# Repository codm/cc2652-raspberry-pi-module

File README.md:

# cod.m ZigBee CC2652P Raspberry Pi module
[ZigBee CC2652 Raspberry Pi Coordinator](https://shop.codm.de/automation/zigbee/33/zigbee-cc2652p2-raspberry-pi-module) - a ZigBee Coordinator designed for the GPIO of the Raspberry Pi running Z-Stack Firmware 3.x - thanks to [Koenkk](https://github.com/Koenkk/).
The used CC2652P is the current generation of microcontrollers for ZigBee 3.x Coordinators and has an integrated power amplifier (+20dBm) for better coverage. 

According to [koenkk](https://github.com/Koenkk/Z-Stack-firmware/tree/master/coordinator) the CC2652 allows for up to 50 direct children and 100/200 routes directly on the coordinator. 
The size of a ZigBee mesh is not defined by the count of possible direct children at the coordinator, see https://www.zigbee2mqtt.io/information/FAQ.html#i-read-that-zigbee2mqtt-has-a-limit-of-20-devices-is-this-true

This module is the successor of our [CC2538 module](https://github.com/codm/cc2538-raspberry-pi-module). This time it is powered via the 5V rail of the Raspberry Pi with an LDO (Low Drop Out) voltage regulator. The CC2538 worked well on 3.3V directly but for the CC2652 we've decided to be not dependent on the internal voltage regulators of the Pi itself. 

You can buy a ready built coordinator, including external antenna at our webshop https://shop.codm.de/automation/zigbee/33/zigbee-cc2652p2-raspberry-pi-module or built on for non commercial use by yourself based on the files in this repository. Use the `bom.ulp` from Eagle to generate a parts list (BOM). 
If you can't get hold of the AP2112K you can also use an TLV75533P.

The 3D model of the RF-Star CC2652P could be found at GrabCad: https://grabcad.com/library/rf-star-cc2652p-module-1

# Running
To us the module directly on the serial interface on the GPIO of the Raspberry Pi, you have to free it up first. Either completely or by moving the Bluetooth UART to the mini-uart.
See https://www.raspberrypi.com/documentation/computers/configuration.html#configuring-uarts for a detailed explanation.

This is also explained in the manual (german): [Anleitung cod.m ZigBee CC2652 Raspberry Pi Modul](https://shop.codm.de/media/pdf/31/38/dd/20210427_ZigBee_CC2652_Raspberry_Pi_Modul_V02_Datenblatt_Anleitung-webnc4XN2YCGznNh.pdf)

If you want to use it with Home Assistant refer to this guide: https://github.com/MarijnPessers/cod.m-CC2538-CC2592-for-Home-Assistant

## zigbee2mqtt
Edit `data/configuration.yaml` accordingly: 

```
serial:
  port: /dev/ttyAMA0
  advanced: 
    baudrate: 115200 
    rtscts: false
```

## Homegear
Install `homegear-zigbee` and edit `/etc/homegear/families/zigbee.conf`: 

```
[Serial]
id = CC2652 
deviceType = serial

#use your own 16 bytes hexadecimal key! 
password = AABBCCDDEEFF11223344556677889900

device = /dev/ttyAMA0
```
Don't forget to comment in the `[]` block.

# Antenna
We recommend to use only external antennas as the module is close to the WiFi and Bluetooth module/antenna on the Raspberry Pi. But if you want to use the attached PCB antenna, rotate the resistor pointing to the u.FL socket by 90° so it connects the PCB trace.

# Firmware
We use Koenkk's Z-Stack 3.x Coordinator Firmware from https://github.com/Koenkk/Z-Stack-firmware/tree/master/coordinator/Z-Stack_3.x.0/bin, ZigStar Variant as it uses the same RF-BM-2652P2.

You can flash the firmware either by JTAG or directly from the Raspberry Pi using [cc2538-prog](https://github.com/1248/cc2538-prog/) - despite the name it also works with the CC2652.
The firmware has the needed serial bootloader enabled.

## JTAG
The 2x05 header is following the common [JTAG-Cortex-M0](https://www.segger.com/products/debug-probes/j-link/accessories/adapters/9-pin-cortex-m-adapter/) Layout.

Use `CC2652R1F` and `JTAG`@4000kHz.

## Serial via GPIO

### cc2538-bsl (preferred)
Install python3 if not alreay present with `sudo apt update && sudo apt-get install python3-pip` and install the needed python libraries `sudo pip3 install pyserial intelhex`.

Download or checkout [cc2538-bsl](https://github.com/JelmerT/cc2538-bsl) into a directory. After that download and extract the wanted coordinator firmware from [https://github.com/Koenkk/Z-Stack-firmware/tree/develop/coordinator/Z-Stack_3.x.0/bin](https://github.com/Koenkk/Z-Stack-firmware/tree/master/coordinator/Z-Stack_3.x.0/bin) - for the cod.m CC2652 Raspberry Pi module you'll need `CC1352P2_CC2652P_launchpad_*.zip` as listed on Koenkk's GitHub.

Please check that you zigbee software is not running anymore an nothing is accessing the serial device where the zigbee module is plugged in (`/dev/ttyAMA0`).

While connected and powered through the Pi, hold down the flash button on the module and press reset shortly while still holding flash. The CC2652 should now be in the bootloder.

To flash type `python3 cc2538-bsl.py -p /dev/ttyAMA0 -evw CC1352P2_CC2652P_launchpad_coordinator_20211217.hex` in the appropriate directory. Change the filename of the .hex-file accordingly.

The output looks something like this: 
```
pi@zigbee:~/cc2538-bsl $ python3 cc2538-bsl.py -evw -p /dev/ttyAMA0 ../CC1352P2_CC2652P_launchpad_coordinator_20211217.hex 
Opening port /dev/ttyAMA0, baud 500000
Reading data from ../CC1352P2_CC2652P_launchpad_coordinator_20211217.hex
Your firmware looks like an Intel Hex file
Connecting to target...
CC1350 PG2.0 (7x7mm): 352KB Flash, 20KB SRAM, CCFG.BL_CONFIG at 0x00057FD8
Primary IEEE Address: 00:12:4B:00:25:8F:18:32
    Performing mass erase
Erasing all main bank flash sectors
    Erase done
Writing 360448 bytes starting at address 0x00000000
Write 104 bytes at 0x00057F980
    Write done                                
Verifying by comparing CRC32 calculations.
    Verified (match: 0xba5c19c5)
```

After that hit the reset button on the module and start your zigbee software again. Maybe you have to replug the module or powercycle the pi.

Thanks to Alex for the documentation of that way.
Alternatively you can use https://github.com/electrolama/llama-bsl but I did not test this yet.

### cc2538-prog
Install and compile [cc2538-prog](https://github.com/1248/cc2538-prog/).

While connected and powered through the Pi, hold down the `flash` button on the module and press `reset` shortly while still holding `flash`. The CC2652 should now be in the bootloder.

Then execute `./cc2538-prog -d /dev/ttyAMA0 -f CC1352P2_CC2652P_launchpad_coordinator_20210120.hex `

The output should look like this: 
```
ping ok
Bootloader detected
Erasing page 0
Erasing page 1
[...]
Erasing page 254
Erasing page 255
Writing 16 bytes to 0x00200000
Writing 16 bytes to 0x00200010
[...]
Writing 16 bytes to 0x0023C7F0
Writing 12 bytes to 0x0027FFD4
```

After that reset the module using the corresponding button. 
It happened sometimes that I had to replug the module to get it to work again. 

# Thanks
* @koenkk Z-Stack Firmware - https://github.com/Koenkk/Z-Stack-firmware
* @1248 cc2538-prog - https://github.com/1248/cc2538-prog/

# License
[CC-BY-NC-SA 3.0](https://creativecommons.org/licenses/by-nc-sa/3.0/)

cod.m GmbH, Patrik Mayer, 2021

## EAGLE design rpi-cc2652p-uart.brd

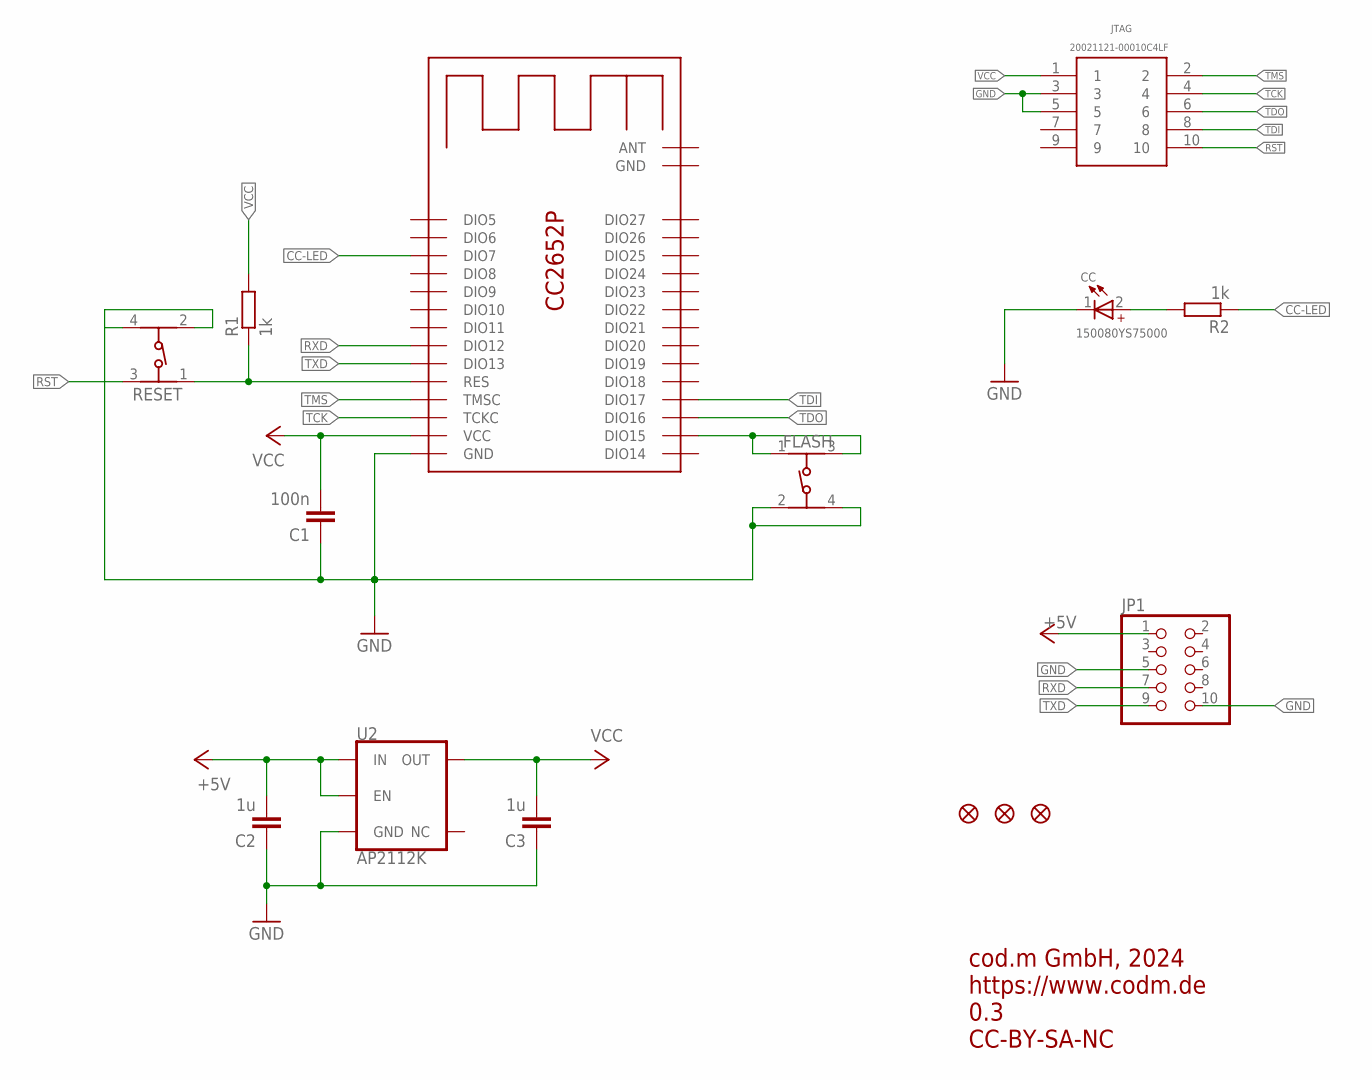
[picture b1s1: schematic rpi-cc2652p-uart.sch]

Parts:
C1: 100n; C0603K
C2, C3: 1u; C0805
CC: 150080YS75000; WL-SMCW_0805
FD1, FD2, FD3: FIDUCIAL1X2; FIDUCIAL-1X2
FLASH: 434153017835
JP1: PINHD-2X5; 2X05
JTAG: 20021121-00010C4LF; 2002112100010C4LF
R1, R2: 1k; R0603RF
RESET: 434153017835
U1: CC2652P2-DUOWEISI
U2: AP2112K; SOT23-5

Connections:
+5V: C2.2, JP1.1, U2.1 (IN), U2.3 (EN)
CC-LED: R2.1, U1.DIO7
FLASH: FLASH.1, FLASH.3 (2), U1.DIO15
GND: C1.1, C2.1, C3.1, CC.1 (-), FLASH.2 (3), FLASH.4, JP1.5, JP1.10, JTAG.3, JTAG.5, RESET.2 (3), RESET.4, U1.GND, U2.2 (GND)
unnamed: CC.2 (+), R2.2
RST: JTAG.10, R1.1, RESET.1, RESET.3 (2), U1.RES
RXD: JP1.7, U1.DIO12
TCK: JTAG.4, U1.TCKC
TDI: JTAG.8, U1.DIO17
TDO: JTAG.6, U1.DIO16
TMS: JTAG.2, U1.TMSC
TXD: JP1.9, U1.DIO13
VCC: C1.2, C3.2, JTAG.1, R1.2, U1.VCC, U2.5 (OUT)

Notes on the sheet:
cod.m GmbH, 2024 https://www.codm.de 0.3 CC-BY-SA-NC

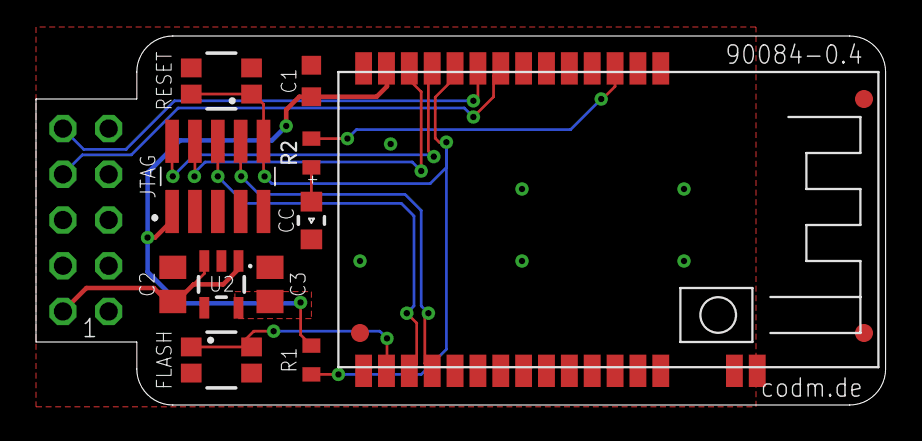
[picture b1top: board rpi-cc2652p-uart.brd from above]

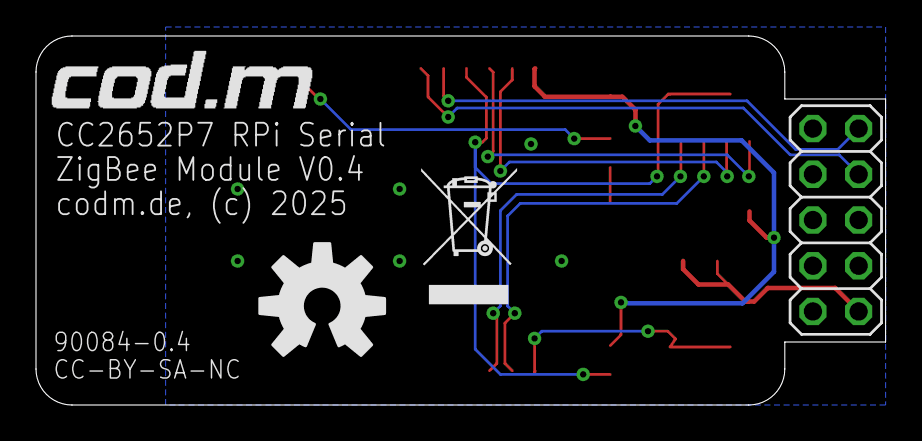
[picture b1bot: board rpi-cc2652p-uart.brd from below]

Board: 2 copper layers, 47.2 x 20.5 mm, 18 parts (4 on the bottom side), 13 nets.

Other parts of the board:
U$2: CODM-LOGO
U$3: WEEE-LOGO-5MM
U$4: OSHW-LOGO-L

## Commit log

2021-04-15 v0.2 with ldo and optimized footprint
2021-04-15 bedder outline
2021-04-28 added readme and images
2021-04-28 refined readme
2021-04-28 fixed homegear config example
2021-06-22 Update README.md
    added instructions for home assistant by @MarijnPessers
2021-12-22 cosmetics on pcb
2021-12-22 added cc2538-bsl instructions for flashing
2022-02-21 Update README.md
    added cc2652p 3d model link
2022-07-20 Update README.md
    corrected z-stack link
2023-06-26 Updated RaspberryPi UART Link
2024-03-23 lib updates
2024-03-23 0805 to 0603
2025-02-24 added CC LED on DIO7
2025-03-24 bom for v0.4
2025-03-24 fixed missing trage

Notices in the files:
rpi-cc2652p-uart.brd:
codm.de, (c) 2025
parts and their libraries:
SparkFun-Aesthetics: Licensing: Creative Commons ShareAlike 4.0 International - https://creativecommons.org/licenses/by-sa/4.0
434153017835_Eagle_WS-TASV_rev20a: Copyright: Würth Elektronik
